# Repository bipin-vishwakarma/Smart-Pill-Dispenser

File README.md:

# 💊 Smart Pill Dispenser

An **ESP32-S3 based automated pill dispenser** — a biomedical hardware project taken end-to-end in **KiCad**: schematic → PCB layout → ERC/DRC → Gerber export → fab-ready.

> Designed to dispense scheduled medication doses reliably — built as a real, manufacturable board, not just a breadboard prototype.

---

## 🔧 From Prototype → Custom Board

<table>
<tr>
<td width="50%" align="center">

<br /><sub><b>① Prototype</b> — Arduino UNO + LCD + servo + buzzer (Tinkercad)</sub>
</td>
<td width="50%" align="center">

<br /><sub><b>② Custom PCB</b> — ESP32-S3 board, designed in KiCad (3D render)</sub>
</td>
</tr>
</table>

The project evolved from a breadboard proof-of-concept into a **custom-routed PCB** — the way real hardware ships.

---

## 🧭 Design Iterations

Seven board revisions capture the full evolution:

| Version | Notes |
|:--|:--|
| `Pill_dispenser` | V2 — early schematic + PCB |
| `Pill_Dispenser_V3` | routing & layout refinement |
| `Pill_Dispenser_1.0` / `V4` | wired revision + **full Gerber & drill export** (fab package) |
| `Pill_Dispenser_V5` | DRC cleanup |
| `Pill_Dispenser_V6` – `V7` | latest revisions |

## ⚙️ Tech

- **MCU:** ESP32-S3
- **EDA:** KiCad (schematic capture + PCB layout)
- **Outputs:** Gerbers, drill files, ERC/DRC-clean design, 3D STEP model
- **Domain:** Biomedical / medication-adherence hardware

## 📂 Opening the project

Install [KiCad](https://www.kicad.org/) (8.x+), then open any version's `.kicad_pro`. Gerbers under `Pill_Dispenser_V4/` can be sent straight to a fab house or previewed in an online Gerber viewer.

---

<sub>Part of my biomedical hardware portfolio · <a href="https://github.com/bipin-vishwakarma">@bipin-vishwakarma</a></sub>

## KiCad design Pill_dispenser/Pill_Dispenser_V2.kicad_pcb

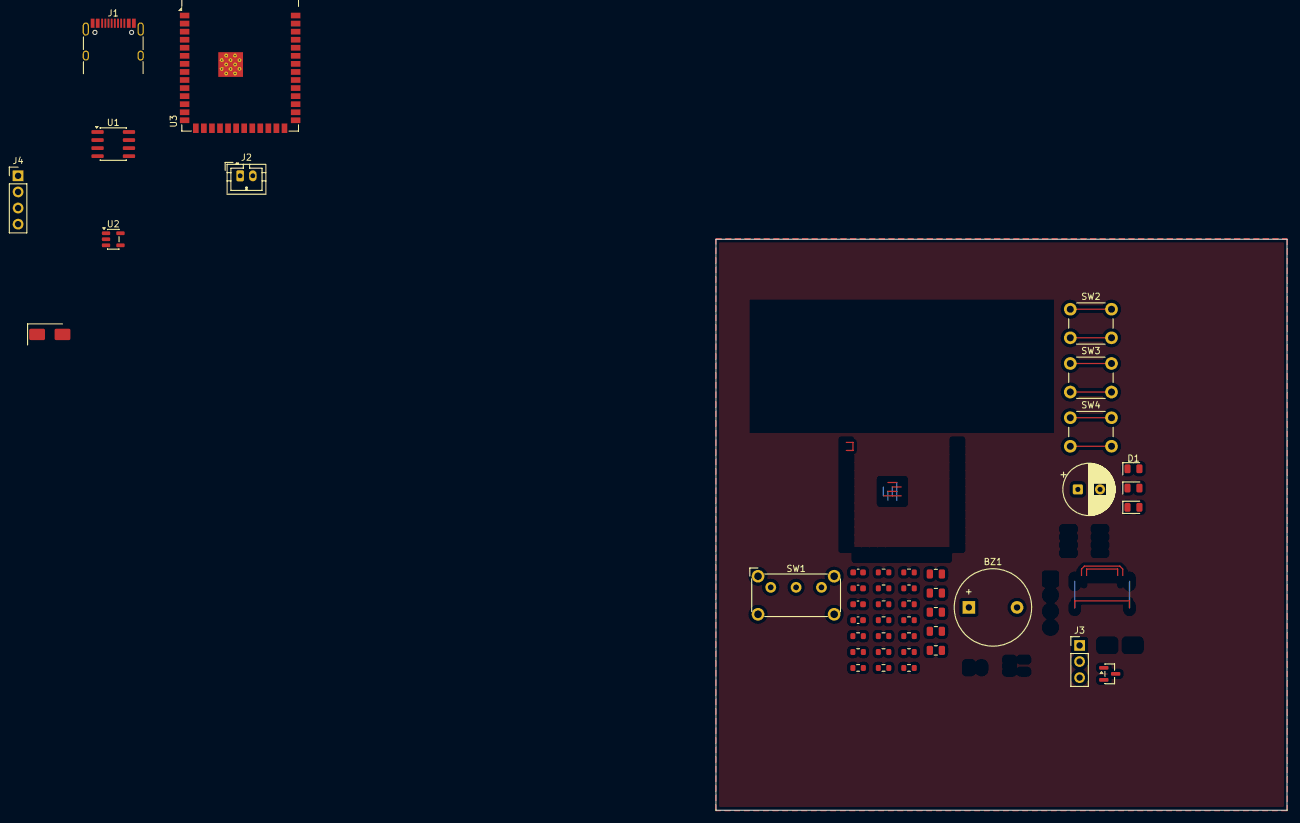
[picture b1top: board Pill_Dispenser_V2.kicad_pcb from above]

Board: 2 copper layers, 90.0 x 90.0 mm, 44 parts (0 on the bottom side), 3 nets.

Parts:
BZ1: Buzzer; Buzzer_12x9.5RM7.6
C1, C3, C4, C9: 10uF; C_0805_2012Metric
C2, C6, C7: 100nF; C_0603_1608Metric
C5: 22uF; C_0805_2012Metric
C8: 1uF; C_0603_1608Metric
C10: 470uF; CP_Radial_D8.0mm_P3.50mm
D1: Red_CHG; LED_0805_2012Metric
D2: Green_STDBY; LED_0805_2012Metric
D3: 1N5819; D_SMA
D4: Red_STATUS; LED_0805_2012Metric
J1: USB-C; USB_C_Receptacle_HRO_TYPE-C-31-M-12
J2: Battery; JST_PH_B2B-PH-K_1x02_P2.00mm_Vertical
J3: SERVO; PinHeader_1x03_P2.54mm_Vertical
J4: OLED; PinHeader_1x04_P2.54mm_Vertical
Q1: MMBT2222A; SOT-23
R1, R2: 5.1K; R_0603_1608Metric
R3, R4: 22; R_0603_1608Metric
R5: 2K; R_0603_1608Metric
R6, R7, R13: 1K; R_0603_1608Metric
R8, R9, R17: 10K; R_0603_1608Metric
R10: 100; R_0603_1608Metric
R11, R12: 4.7K; R_0603_1608Metric
R14: 470; R_0603_1608Metric
R15, R16: 100K; R_0603_1608Metric
SW1: PWR_SW; SW_E-Switch_EG1224_SPDT_Angled
SW2: RESET; SW_PUSH_6mm_H5mm
SW3: BOOT; SW_PUSH_6mm_H5mm
SW4: USER; SW_PUSH_6mm_H5mm
U1: TP4056; SOIC-8_3.9x4.9mm_P1.27mm
U2: AP2112K-3.3; SOT-23-5
U3: ESP32-S3-MINI-1; ESP32-S3-WROOM-1

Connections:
unnamed: J1.A1 (GND), J1.A12 (GND), J1.B1 (GND), J1.B12 (GND)
unnamed: J1.A4 (VBUS), J1.A9 (VBUS), J1.B4 (VBUS), J1.B9 (VBUS)
unnamed: U3.1 (GND), U3.2 (GND)

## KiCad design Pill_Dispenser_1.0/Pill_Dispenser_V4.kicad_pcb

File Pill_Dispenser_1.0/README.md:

# 💊 Smart Pill Dispenser 1.0 - ESP32-S3 Powered

## 🚀 Overview

The **Pill Dispenser 1.0** is a high-performance, compact, and automated solution for medication management. Powered by an **ESP32-S3**, this version integrates smart scheduling, Li-Ion battery management, and an OLED interface for a seamless user experience.

Designed with precision in **KiCad**, the PCB is optimized for a **50mm x 40mm** footprint, making it ideal for portable or space-constrained medical IoT applications.

---

## ✨ Key Features

- 🧠 **ESP32-S3-WROOM-1**: High-performance dual-core MCU with Wi-Fi & Bluetooth.
- 🔋 **Li-Ion Management**: Integrated TP4056 charging circuit via USB-C.
- ⚙️ **Mechanism**: Precise servo motor control for rotating pill compartments.
- 🖥️ **User Interface**: 128x64 OLED display for status alerts and pill reminders.
- 🔔 **Alert System**: Onboard SMD buzzer (via transistor driver) and multi-color status LEDs.
- 🔌 **USB-C Connectivity**: Modern power delivery and data access.
- 📏 **Compact PCB**: 2-layer design (50x40mm) with optimized SMD placement.

---

## 🛠️ Hardware Specifications

### Power Section
- **Charger IC**: TP4056 (USB-C 5V Input)
- **LDO**: AP2112K-3.3V (600mA low-noise)
- **Protection**: 1N5819 Schottky reverse polarity protection.

### Microcontroller Section
- **MCU**: ESP32-S3-WROOM-1 (4MB Flash)
- **Buttons**: Boot, Reset, and a dedicated User Input button.
- **I2C Pull-ups**: 4.7kΩ on SDA/SCL.

### Peripherals
- **OLED**: I2C Interface (GND, VCC, SCL, SDA)
- **Servo**: 3-pin standard header (PWM controlled)
- **Buzzer**: SMD 5020 with MMBT2222A driver.

---

## 📁 Repository Structure

```text
├── assets/                  # High-quality project renders and visual assets
├── gerbers/                 # PCB manufacturing files (RS-274X)
├── bom/                     # Bill of Materials (CSV/PDF)
├── Pill_Dispenser_V4.kicad_pcb  # Main PCB Layout
├── Pill_Dispenser_V4.kicad_sch  # Main Schematic
├── LICENSE                  # MIT License
└── README.md                # Project documentation
```

---

## 🏗️ Getting Started

### Design Files
The hardware was designed using **KiCad 8.0+**. To view or modify the project:
1. Clone the repository.
2. Open `Pill_Dispenser_V4.kicad_pro`.
3. Ensure the required library footprints are linked (or use the built-in caches).

### Manufacturing
The `Pill_Dispenser_V4_Gerber.zip` contains all necessary files for fabrication (JLCPCB, PCBWay, etc.).
- **Material**: FR4
- **Thickness**: 1.6mm
- **Finish**: Lead-free HASL (Recommended)

---

## 📜 License

This project is licensed under the **MIT License** - see the [LICENSE](LICENSE) file for details.

---

## 🌍 Connect
*Feel free to star the repo ⭐️ if you find this useful!*

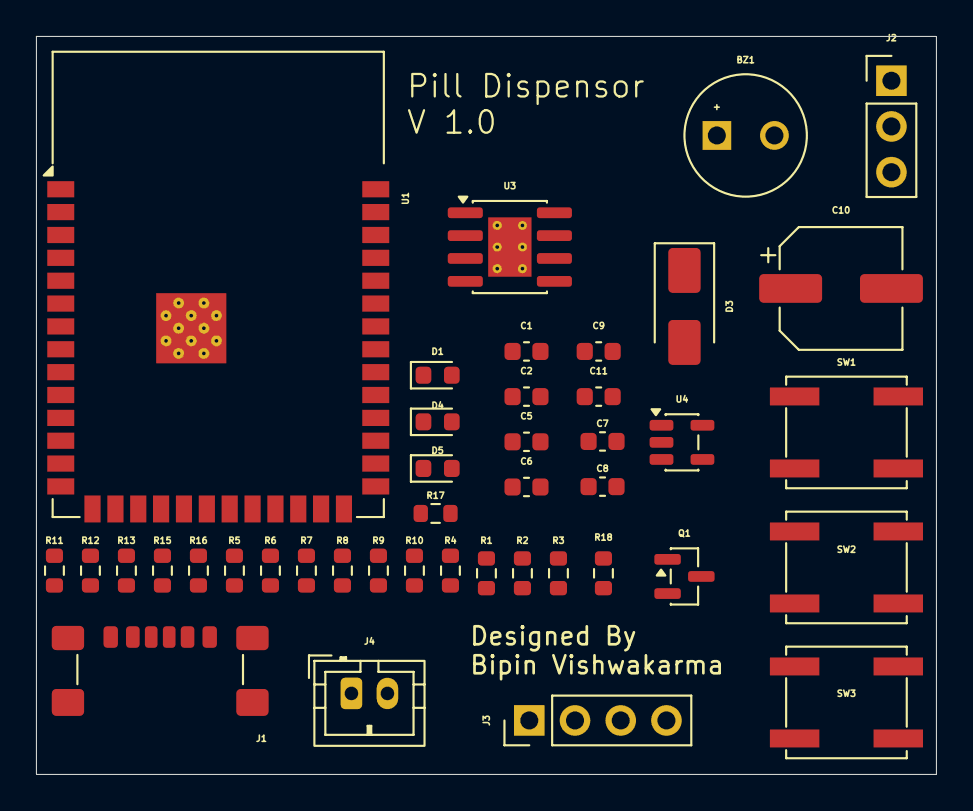
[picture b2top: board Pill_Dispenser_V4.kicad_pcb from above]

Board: 2 copper layers, 50.0 x 41.0 mm, 42 parts (0 on the bottom side), 25 nets, no tracks yet.

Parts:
BZ1: Buzzer; MagneticBuzzer_Kingstate_KCG0601
C1, C2, C9: 10uF; C_0603_1608Metric
C5, C6, C7, C8, C11: 100nF; C_0603_1608Metric
C10: 100uF; CP_Elec_6.3x5.4
D1: STATUS; LED_0603_1608Metric
D3: 1N5819; D_SMA
D4: CHRG; LED_0603_1608Metric
D5: STDBY; LED_0603_1608Metric
J1: USB-C; USB_C_Receptacle_GCT_USB4135-GF-A_6P_TopMnt_Horizontal
J2: SERVO; PinHeader_1x03_P2.54mm_Vertical
J3: OLED; PinHeader_1x04_P2.54mm_Vertical
J4: BATTERY; JST_PH_B2B-PH-K_1x02_P2.00mm_Vertical
Q1: MMBT2222A; SOT-23
R1, R13: 330; R_0603_1608Metric
R2, R4, R18: 1k; R_0603_1608Metric
R3, R8, R17: 10k; R_0603_1608Metric
R5: 2k; R_0603_1608Metric
R6, R7: 4.7k; R_0603_1608Metric
R9, R10: 100k; R_0603_1608Metric
R11, R12: 5.1k; R_0603_1608Metric
R15, R16: 22; R_0603_1608Metric
SW1: USER; SW_SPST_EVQP0
SW2: BOOT; SW_SPST_EVQP0
SW3: RESET; SW_SPST_EVQP0
U1: ESP32-S3-WROOM-1
U3: TP4056-42-ESOP8; SOIC-8-1EP_3.9x4.9mm_P1.27mm_EP2.41x3.3mm_ThermalVias
U4: AP2112K-3.3; SOT-23-5

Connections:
/3V3: BZ1.1 (+), C2.1, C5.1, C6.1, C7.1, C8.1, C9.1, C11.2, J3.1, R2.2, R3.1, R5.1, R6.2, R7.2, R8.1, R9.1, R13.2, R17.2, R18.2, U1.2 (3V3), U4.3 (EN), U4.5 (VOUT)
/CHRG: D4.1 (K), U3.7 (~CHRG)
/SCL: J3.4, R7.1, U1.17 (IO9)
/SDA: J3.3, R6.1, U1.12 (IO8)
/STATUS: R1.2, U1.39 (IO1)
/STDBY: D5.1 (K), U3.6 (~STDBY)
/USB_DN: J1.7, R15.2
/USB_DP: J1.6, R16.2
/VBAT: C1.1, C10.1, J2.2, J4.1, U3.5 (BAT), U4.1 (VIN)
/VBUS: D3.2 (A), J1.4, J1.9, U3.8 (CE)
GND: C1.2, C2.2, C5.2, C6.2, C7.2, C8.2, C9.2, C10.2, C11.1, D1.1 (K), J1.1, J1.2, J2.1, J3.2, J4.2, Q1.2 (C), R11.2, R12.2, SW1.1, SW2.1, SW3.1, U1.1 (GND), U1.40 (GND), U1.41 (GND), U3.1 (TEMP), U3.3 (GND), U3.9 (EPAD), U4.2 (GND)
unnamed: BZ1.2 (-), Q1.3 (E)
unnamed: D1.2 (A), R1.1
unnamed: D3.1 (K), U3.4 (V_{CC})
unnamed: D4.2 (A), R2.1
unnamed: D5.2 (A), R18.1
unnamed: J1.5, R11.1
unnamed: J2.3, U1.4 (IO4)
unnamed: Q1.1 (B), R4.1
unnamed: R3.2, SW3.2, U1.3 (EN)
unnamed: R8.2, SW2.2, U1.27 (IO0)
unnamed: R4.2, U1.5 (IO5)
unnamed: R17.1, SW1.2, U1.18 (IO10)
unnamed: R16.1, U1.14 (USB_D+)
unnamed: R15.1, U1.13 (USB_D-)

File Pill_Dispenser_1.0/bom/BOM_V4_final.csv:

"Refs","Value","Footprint","Qty","DNP"
"BZ1","Buzzer","Buzzer_Beeper:MagneticBuzzer_Kingstate_KCG0601","1",""
"C1","10uF","Capacitor_SMD:C_0603_1608Metric","1",""
"C2","10uF","Capacitor_SMD:C_0603_1608Metric","1",""
"C5","100nF","Capacitor_SMD:C_0603_1608Metric","1",""
"C6","100nF","Capacitor_SMD:C_0603_1608Metric","1",""
"C7","100nF","Capacitor_SMD:C_0603_1608Metric","1",""
"C8","100nF","Capacitor_SMD:C_0603_1608Metric","1",""
"C9","10uF","Capacitor_SMD:C_0603_1608Metric","1",""
"C10","100uF","Capacitor_SMD:CP_Elec_6.3x5.4","1",""
"C11","100nF","Capacitor_SMD:C_0603_1608Metric","1",""
"D1","STATUS","LED_SMD:LED_0603_1608Metric","1",""
"D3","1N5819","Diode_SMD:D_SMA","1",""
"D4","CHRG","LED_SMD:LED_0603_1608Metric","1",""
"D5","STDBY","LED_SMD:LED_0603_1608Metric","1",""
"J1","USB-C","Connector_USB:USB_C_Receptacle_GCT_USB4135-GF-A_6P_TopMnt_Horizontal","1",""
"J2","SERVO","Connector_PinHeader_2.54mm:PinHeader_1x03_P2.54mm_Vertical","1",""
"J3","OLED","Connector_PinHeader_2.54mm:PinHeader_1x04_P2.54mm_Vertical","1",""
"J4","BATTERY","Connector_JST:JST_PH_B2B-PH-K_1x02_P2.00mm_Vertical","1",""
"Q1","MMBT2222A","Package_TO_SOT_SMD:SOT-23","1",""
"R1","330","Resistor_SMD:R_0603_1608Metric","1",""
"R2","330","Resistor_SMD:R_0603_1608Metric","1",""
"R3","10k","Resistor_SMD:R_0603_1608Metric","1",""
"R4","1k","Resistor_SMD:R_0603_1608Metric","1",""
"R5","2k","Resistor_SMD:R_0603_1608Metric","1",""
"R6","4.7k","Resistor_SMD:R_0603_1608Metric","1",""
"R7","4.7k","Resistor_SMD:R_0603_1608Metric","1",""
"R8","10k","Resistor_SMD:R_0603_1608Metric","1",""
"R9","100k","Resistor_SMD:R_0603_1608Metric","1",""
"R10","100k","Resistor_SMD:R_0603_1608Metric","1",""
"R11","5.1k","Resistor_SMD:R_0603_1608Metric","1",""
"R12","5.1k","Resistor_SMD:R_0603_1608Metric","1",""
"R13","330","Resistor_SMD:R_0603_1608Metric","1",""
"R15","22","Resistor_SMD:R_0603_1608Metric","1",""
"R16","22","Resistor_SMD:R_0603_1608Metric","1",""
"R17","10k","Resistor_SMD:R_0603_1608Metric","1",""
"SW1","USER","Button_Switch_SMD:SW_SPST_EVQP0","1",""
"SW2","BOOT","Button_Switch_SMD:SW_SPST_EVQP0","1",""
"SW3","RESET","Button_Switch_SMD:SW_SPST_EVQP0","1",""
"U1","ESP32-S3-WROOM-1","RF_Module:ESP32-S3-WROOM-1","1",""
"U3","TP4056-42-ESOP8","Package_SO:SOIC-8-1EP_3.9x4.9mm_P1.27mm_EP2.41x3.3mm_ThermalVias","1",""
"U4","AP2112K-3.3","Package_TO_SOT_SMD:SOT-23-5","1",""
